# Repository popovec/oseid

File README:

Description

AVR128DA32 microcontroller based open source EID smartcard with RSA
(512-2048) and ECC - ECDSA and ECDH operations on prime192v1, prime256v1,
secp384r1, secp256k1 and secp521r1. Compatible with MyEID card from Aventra.
Supported in windows and linux by opensc package.  Allow about 64KiB space
for keys/certificates. PKCS#15 structure supported.

USB token with CCID interface based on atmel xmega128a4u with same features as card.

USB token based on ST LINK V2 (STM32F102CB/STM32F103CB/MH2103CB ARM processor).

Online HTML doc https://popovec.github.io/OsEID/

PDF documentation available at https://oseid.sourceforge.io

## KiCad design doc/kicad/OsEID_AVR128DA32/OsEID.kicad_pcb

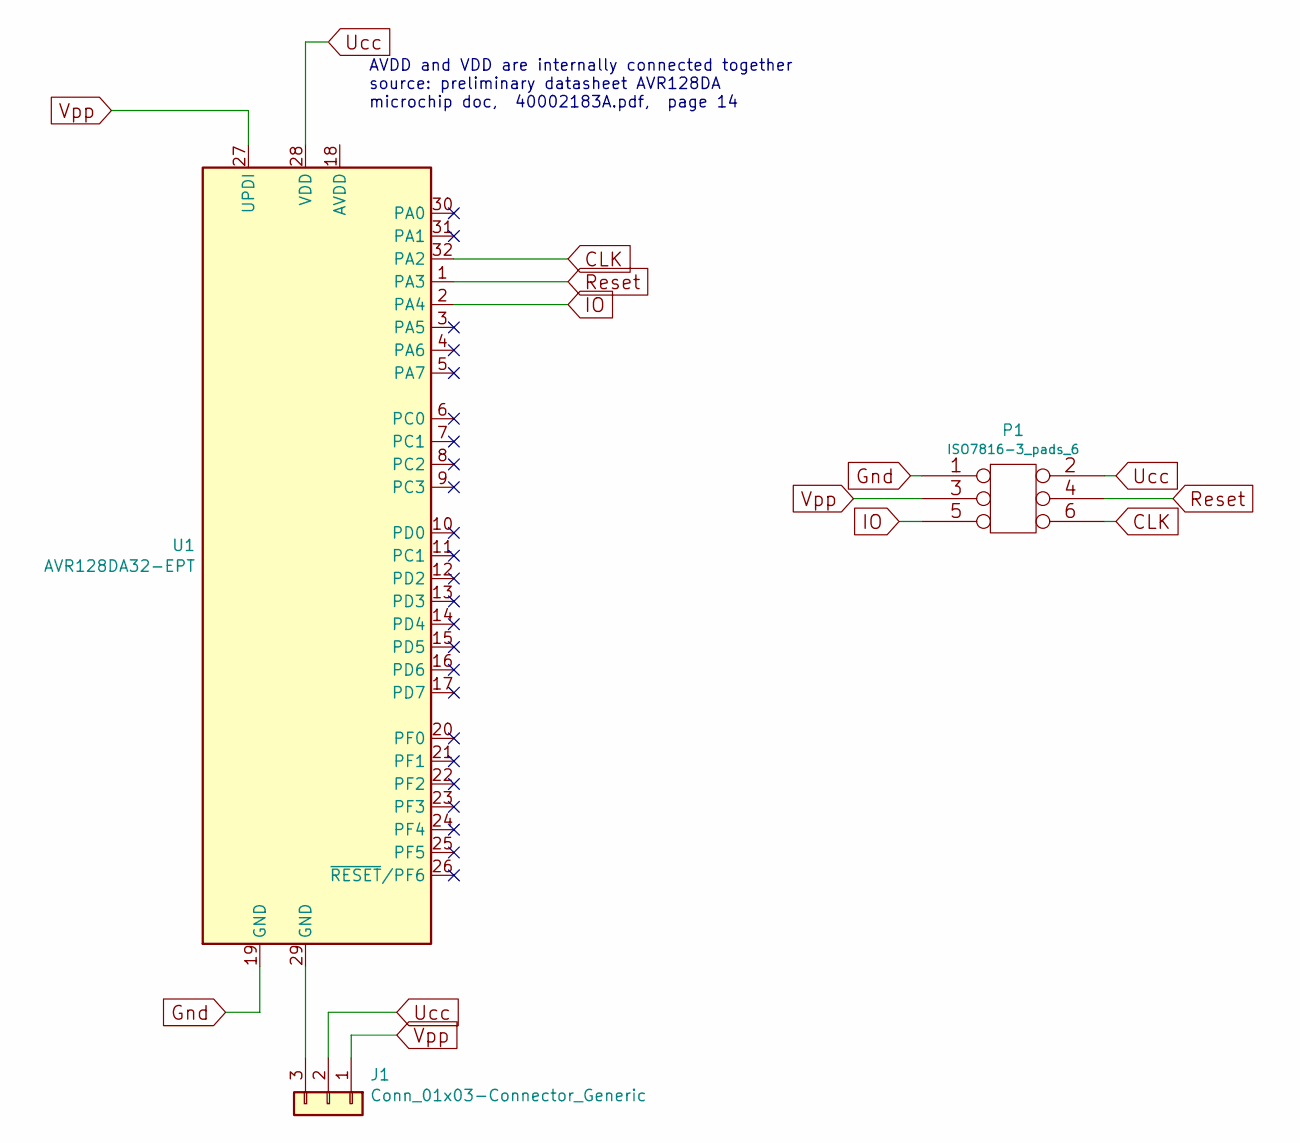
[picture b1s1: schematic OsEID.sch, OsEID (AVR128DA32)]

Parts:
J1: Conn_01x03-Connector_Generic; PIN_ARRAY_3X1
P1: ISO7816-3_pads_6
U1: AVR128DA32-EPT; TQFP-32_7x7mm_P0.8mm

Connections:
CLK: P1.6, U1.32 (PA2)
Gnd: P1.1, U1.19 (GND)
IO: P1.5, U1.2 (PA4)
unnamed: J1.3, U1.29 (GND)
Reset: P1.4, U1.1 (PA3)
Ucc: J1.2, P1.2, U1.28 (VDD)
Vpp: J1.1, P1.3, U1.27 (UPDI)

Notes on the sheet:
AVDD and VDD are internally connected together source: preliminary datasheet AVR128DA microchip doc, 40002183A.pdf, page 14

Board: 2 copper layers, 3 parts (1 on the bottom side), 7 nets.

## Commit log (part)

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2017-01-04 Initial commit (imported from https://oseid.sourceforge.io)
2017-07-03 Version 20170630 commit (imported from https://oseid.sourceforge.io)
2018-01-23 Version 20171231 commit (imported from https://oseid.sourceforge.io)
2018-01-23 ECC: fix blinding (not blinded key was always used)
2019-01-02 Version 20190102 commit (imported from https://oseid.sourceforge.io)
2019-05-23 Move licence to top level dir
    renamed: src/Licence.txt -> Licence.txt
2019-05-23 README update (curve secp521r1)
    modified: README
2019-05-23 Allow max_recv_size = 256 in read binary command.
    modified: src/card_os/fs.c
    modified: src/card_os/iso7816.c
2019-05-23 AVR ASM fix, propagation of carry flag - wrong registers order
    modified: src/lib/avr/mp_mul_256.S
2019-05-23 Create a temporary directory at the beginning.
    modified: src/targets/console/pcscd/OsEIDsim/run_pcscd.sh
2019-06-12 backport from devel
    turn off debug messages (simulator)
    allow upload 56 bit DES key
    OsEID-tool - allow AES/DES keys upload
    OsEID-tool - allow specify reader in env variable
2019-06-17 EC key upload - reject incorrect APDU (similar to MyEID)
    MyEID does not allow upload incorrectly prefixed EC key.
    OsEID-tool - do not return error for wrong EC key upload
    (waiting for OpenSC #1702)
2019-07-09 backport from devel
    fixed card_io.c for simulator
    OsEID-tool fixes
2019-08-27 Changelog file in doc dir
2019-08-27 Random number generator tests by dieharder
2019-08-27 PDF documentation build script
    Asciidoc source file and build script added.
    Images are cloned from github (html doc)
2019-09-10 coverity scan: false positive out-of-bound-access
2019-09-10 coverity scan: always set reader_fd to -1 on error
    modified: src/targets/console/pcscd/OsEIDsim/serial.c
2019-09-10 rsa: MR test improved
2019-09-20 New release 201909XX-rc2
    (export from development repository)
2019-09-30 Version 20190930 commit (imported from https://oseid.sourceforge.io)
2020-11-16 AVR128DA based OsEID card - kicad files
    PCB and schematics - initial commit
2020-11-16 Allow use HARDWARE SERIAL number of device as CARD serial number
    There is serial number of device available in XMEGA and AVR128DA MCU.
    We can use this serial numbers as card serial number.
    modified: src/card_os/myeid_emu.c
    modified: src/card_os/myeid_emu.h
2020-11-16 DES, do not use 56 bit key
    MyEID card uses 64 bit key. 56 bit key support is for now disabled
    in OsEID device (to save flash size).
    modified: src/card_os/des.c
    modified: src/lib/avr/des.S
2020-11-16 AVR 521 multiplication fix
    Upper part of result is cleared, old code uses fixed number of bytes,
    now MP_BYTES is used to determine how many bytes is to be cleared.
    modified: src/lib/avr/mp_mul_521.S
2020-11-16 AVR asm - squaring (192..1024) improvements
    modified: src/lib/avr/mp_square.S
2020-11-16 For devices with small EEPROMs, allow use reduced PIN structure.
    modified: src/card_os/fs.c
2020-11-16 ASM version for AVR - fast reduction for all supported curves
    Initial patch, no makefile changes.
    modified: src/card_os/bn_lib.h
    modified: src/card_os/ec.c
    new file: src/lib/avr/ec_fast_red.S
    modified: src/lib/avr/rsa.S
    modified: src/lib/generic/bn_lib.c
2020-11-16 Enable ASM fast reduction for all AVR targets
    also remove 56 bit DES key from all targets
    modified: src/Makefile.atmega128
    modified: src/Makefile.console
    modified: src/Makefile.simulavr
    modified: src/Makefile.simulavr1284
    modified: src/targets/simulavr/Readme
2020-11-16 AVR128DA based card - device dependent files
    new file: download/OsEID_AVR128DA32_card_PCB_gerber.pho
    new file: src/Makefile.AVR128DA
    new file: src/targets/AVR128DA/avr.S
    new file: src/targets/AVR128DA/card_io.S
    new file: src/targets/AVR128DA/constants.c
    new file: src/targets/AVR128DA/device-specs/specs-avr128da32
2020-11-16 Profile file for next OpenSC ersion
    new file: download/oseid_0.21.profile
2020-11-16 Improved AVR version - rsa_mul_512()
    modified: src/lib/avr/mp_mul_32.S
2020-11-18 oseid-simulavr patch is now deprecated.
    To test OsEID project with simulavr please use GIT repo:
    https://github.com/popovec/oseid-simulavr
    deleted: src/targets/simulavr/compile_simulavr.sh
    deleted: src/targets/simulavr/oseid-simulavr.patch
2020-11-30 20201130 - release (final hex files, doc)
2020-12-14 pkcs11 ECDSA sign tests with several mechanisms
    ECDSA-SHA1, SHA224, SHA256, SHA384 and SHA512 mechanism tests.
    Warning, working only with patched opensc.., waiting for:
    https://github.com/OpenSC/OpenSC/issues/2181
    modified: tools/OsEID-tool
2021-07-01 20210701 - release (final hex files, doc)
2021-12-18 OsEID-tool: test AES encryption
    modified: OsEID-tool
2021-12-23 The deprecated 'rsautl' command is replaced by the 'pkeyutl' command.
2021-12-27 OsEID-tool: OAEP RSA decrypt test
2022-01-19 coverity check action
    new file: .github/workflows/coverity.yml
2022-01-22 LibreSSL enforces pkeyopt to come after inkey
2022-01-24 fixes RSA calculation for keys where Q > P
    openssl 3.0 does not sort the prime numbers P and Q, in about half of the
    cases it is P > Q.
2022-09-18 OsEID-tool - improved error checking
    modified: tools/OsEID-tool
2022-09-23 T1 transport for AVR targets (AVR128DA and xmega)
    new file: src/card_os/T1_transport.c
2022-09-23 Github actions: crosscompilation for AVR targets
    modified: .github/workflows/oseid-github-ci-test.yaml
2022-09-23 Initial implementation of the change_counter
    Warning, AVR devices (including simulavr) do not yet support real
    change_counter. The change_counter value is always 1.
    modified: src/card_os/mem_device.h
    modified: src/card_os/myeid_emu.c
    modified: src/targets/AVR128DA/mem_device.S
    modified: src/targets/atmega128/mem_device.S
2022-09-25 AVR128DA - change_counter implementation
    modified: src/Makefile.AVR128DA
    modified: src/targets/AVR128DA/mem_device.S
2023-04-21 added bn_is_one() function
    modified: src/card_os/bn_lib.h
    modified: src/lib/generic/bn_lib.c
2023-04-21 OsEID-tool: Do not warn if OpenSC version 0.23 is used.
2023-04-21 OsEID-tool: more tests
    symmetric encrypt/decrypt test included in FULL-TEST
    RSA calculation test for a key in which Q > P
2023-04-21 Fixed 3DES decipher operation.
    modified: src/card_os/myeid_emu.c
2023-04-21 change_counter for atmega128, xmega128a4, simulavr
    Improved card erase.
    modified: src/Makefile.AVR128DA
    modified: src/Makefile.xmega128a4u
    modified: src/card_os/fs.c
    modified: src/card_os/mem_device.h
    modified: src/targets/AVR128DA/mem_device.S
2023-04-21 OsEID profile for OpenSC 0.23
2023-04-21 Fixed asm code for DES/3DES on AVR128DA device.
    modified: src/Makefile.AVR128DA
    modified: src/lib/avr/des.S
2023-04-21 Fixed check for template type in MSE command.
    modified: src/card_os/myeid_emu.c
2023-04-21 Updated links to the ISO7816 standard
    modified: src/card_os/iso7816.c
2023-04-24 AVR implementation bn_is_one()
    modified: src/lib/avr/mp.S
2023-04-24 do not use mp_is_zero if mp_is_one() can be used
    modified: src/card_os/rsa.c
2023-06-26 simulavr: fill eeprom with 0xff
    also fixed the missing slash in the path to the simulavr
    modified: targets/simulavr/constants.c
    modified: targets/simulavr/run_pcscd.sh
2023-07-21 OsEID-tool: Enable use of OpenSSL version 3.X for CSR generation.
2023-09-12 tools: Add support to run the opensc tools under valgrind
2023-09-13 OsEID-tool: use "opensc-tool" instead of "scriptor"
    modified: tools/OsEID-tool
2023-09-13 PPS signaling improved
    modified: src/Makefile.AVR128DA
    modified: src/Makefile.console
    modified: src/card_os/card_io.h
    modified: src/card_os/iso7816.c
    modified: src/targets/AVR128DA/card_io.S
    modified: src/targets/console/card_io.c
2023-09-13 atmega128: refactor card_io.S
    Support for:
    1. Specific mode (protocol T0 or T1)
    2. Negotiated mode (protocol T0 or T1 or both)
    3. speed up to 300 kbits/s (Tested, reader clock 4.8MHz)
    modified: src/Makefile.atmega128
    modified: src/targets/atmega128/card_io.S
2023-09-13 AVR128DA32: C implementation for card_io code (card_io.c)
    new file: src/targets/AVR128DA/card_io.c
2023-09-23 Remmoving card_io_stop_null()
    After the request to extend the working time (sending NULL for T0 protocol
    and WTX frame for T1 protocol), it is not necessary to cancel this request.
    The card_io_tx() function takes care of this.
    modified: src/card_os/card_io.h
    modified: src/card_os/iso7816.c
    modified: src/targets/AVR128DA/card_io.S
2023-10-13 OsEID-tool: do not print warning for OpenSC ver. 0.24
    modified: tools/OsEID-tool
2023-11-18 PIN test improved
    modified: src/card_os/fs.c
2023-12-22 Padding fix (pkcs#1 type 2 padding)
    modified: src/card_os/myeid_emu.c
    modified: src/card_os/rsa.c
    modified: src/card_os/rsa.h
    modified: src/lib/avr/rsa.S
    modified: tools/OsEID-tool
2024-02-20 Improved padding removal.
    Includes AVR code size reduction
    modified: src/card_os/myeid_emu.c
    modified: src/card_os/rsa.c
    modified: src/card_os/rsa.h
    modified: src/lib/avr/rsa.S
2024-02-20 The tables contain constant data, we add the qualifier "const".
    modified: src/card_os/des.c
    modified: src/card_os/iso7816.c
2024-02-24 OsEID port to ARM STM32F102 / STLINK V2
    initial commit
    modified: .github/workflows/oseid-github-ci-test.yaml
    modified: README
    new file: src/Makefile.STM32F102
    modified: src/card_os/debug.h
    new file: src/lib/ARM/bn_lib_arm_cm3.c
2024-02-24 ARM match routines improvements.
    modified: src/lib/ARM/bn_lib_arm_cm3.c
2024-02-24 EC: do not use multiplication if squaring is available.
    modified: src/Makefile.STM32F102
2024-03-03 Improvements to the ARM CM3 "big number" library
    RSA2048: (raw time, from APDU commant to APDU response)
    STM32F102 at 48MHz 1.871s
    STM32F102 at 72MHz 1.374s
    MH2103A at 72MHz 1.185s
    MH2103A at 96MHz 0.891s
    modified: src/lib/ARM/bn_lib_arm_cm3.c
2024-03-03 Parameterization of variables according to processor type
    The size of RAM, FLASH and operating frequency is selected in the Makefile
    according to the type of processor.
    modified: .github/workflows/oseid-github-ci-test.yaml
    modified: README
    renamed: src/Makefile.STM32F102 -> src/Makefile.STM32F10x
    deleted: src/targets/STM32F102/MH2103A.cfg
2024-03-14 If PB12 is grounded after power on, turn RED led on.
    This simplifies token reprogramming.
    modified: src/targets/STM32F10x/STM32F10x_dev_init.c
2024-03-15 USB transfer fix (tested on WIN)
    modified: src/targets/STM32F10x/STM32F10x_dev_init.c
2024-03-15 Doc update
    modified: doc/doc.txt
2025-01-16 github CI: use v4 of the artifact actions
    modified: .github/workflows/oseid-github-ci-test.yaml
2025-01-16 Enable access to reader (Polkit)
    also adjusts "card power up" for OsEIDsim reader.
    new file: .github/001-enable-pcscd.rules
    modified: .github/workflows/oseid-github-ci-test.yaml
    modified: src/targets/console/pcscd/OsEIDsim/ifdhandler.c
2025-01-16 AVR_GCC: for newer versions of gcc just write a warning, don't consider it an error modified: src/targets/atmega128/avr.c modified: src/targets/simulavr/avr.c modified: src/targets/xmega128a4u/avr_os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
2025-04-01 README: update about the token built on the ST LINK V2 programmer.
